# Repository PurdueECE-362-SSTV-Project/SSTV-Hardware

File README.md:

# SSTV-Hardware
This repo contains the SCHEM and PCB files for the SSTV Receiver.

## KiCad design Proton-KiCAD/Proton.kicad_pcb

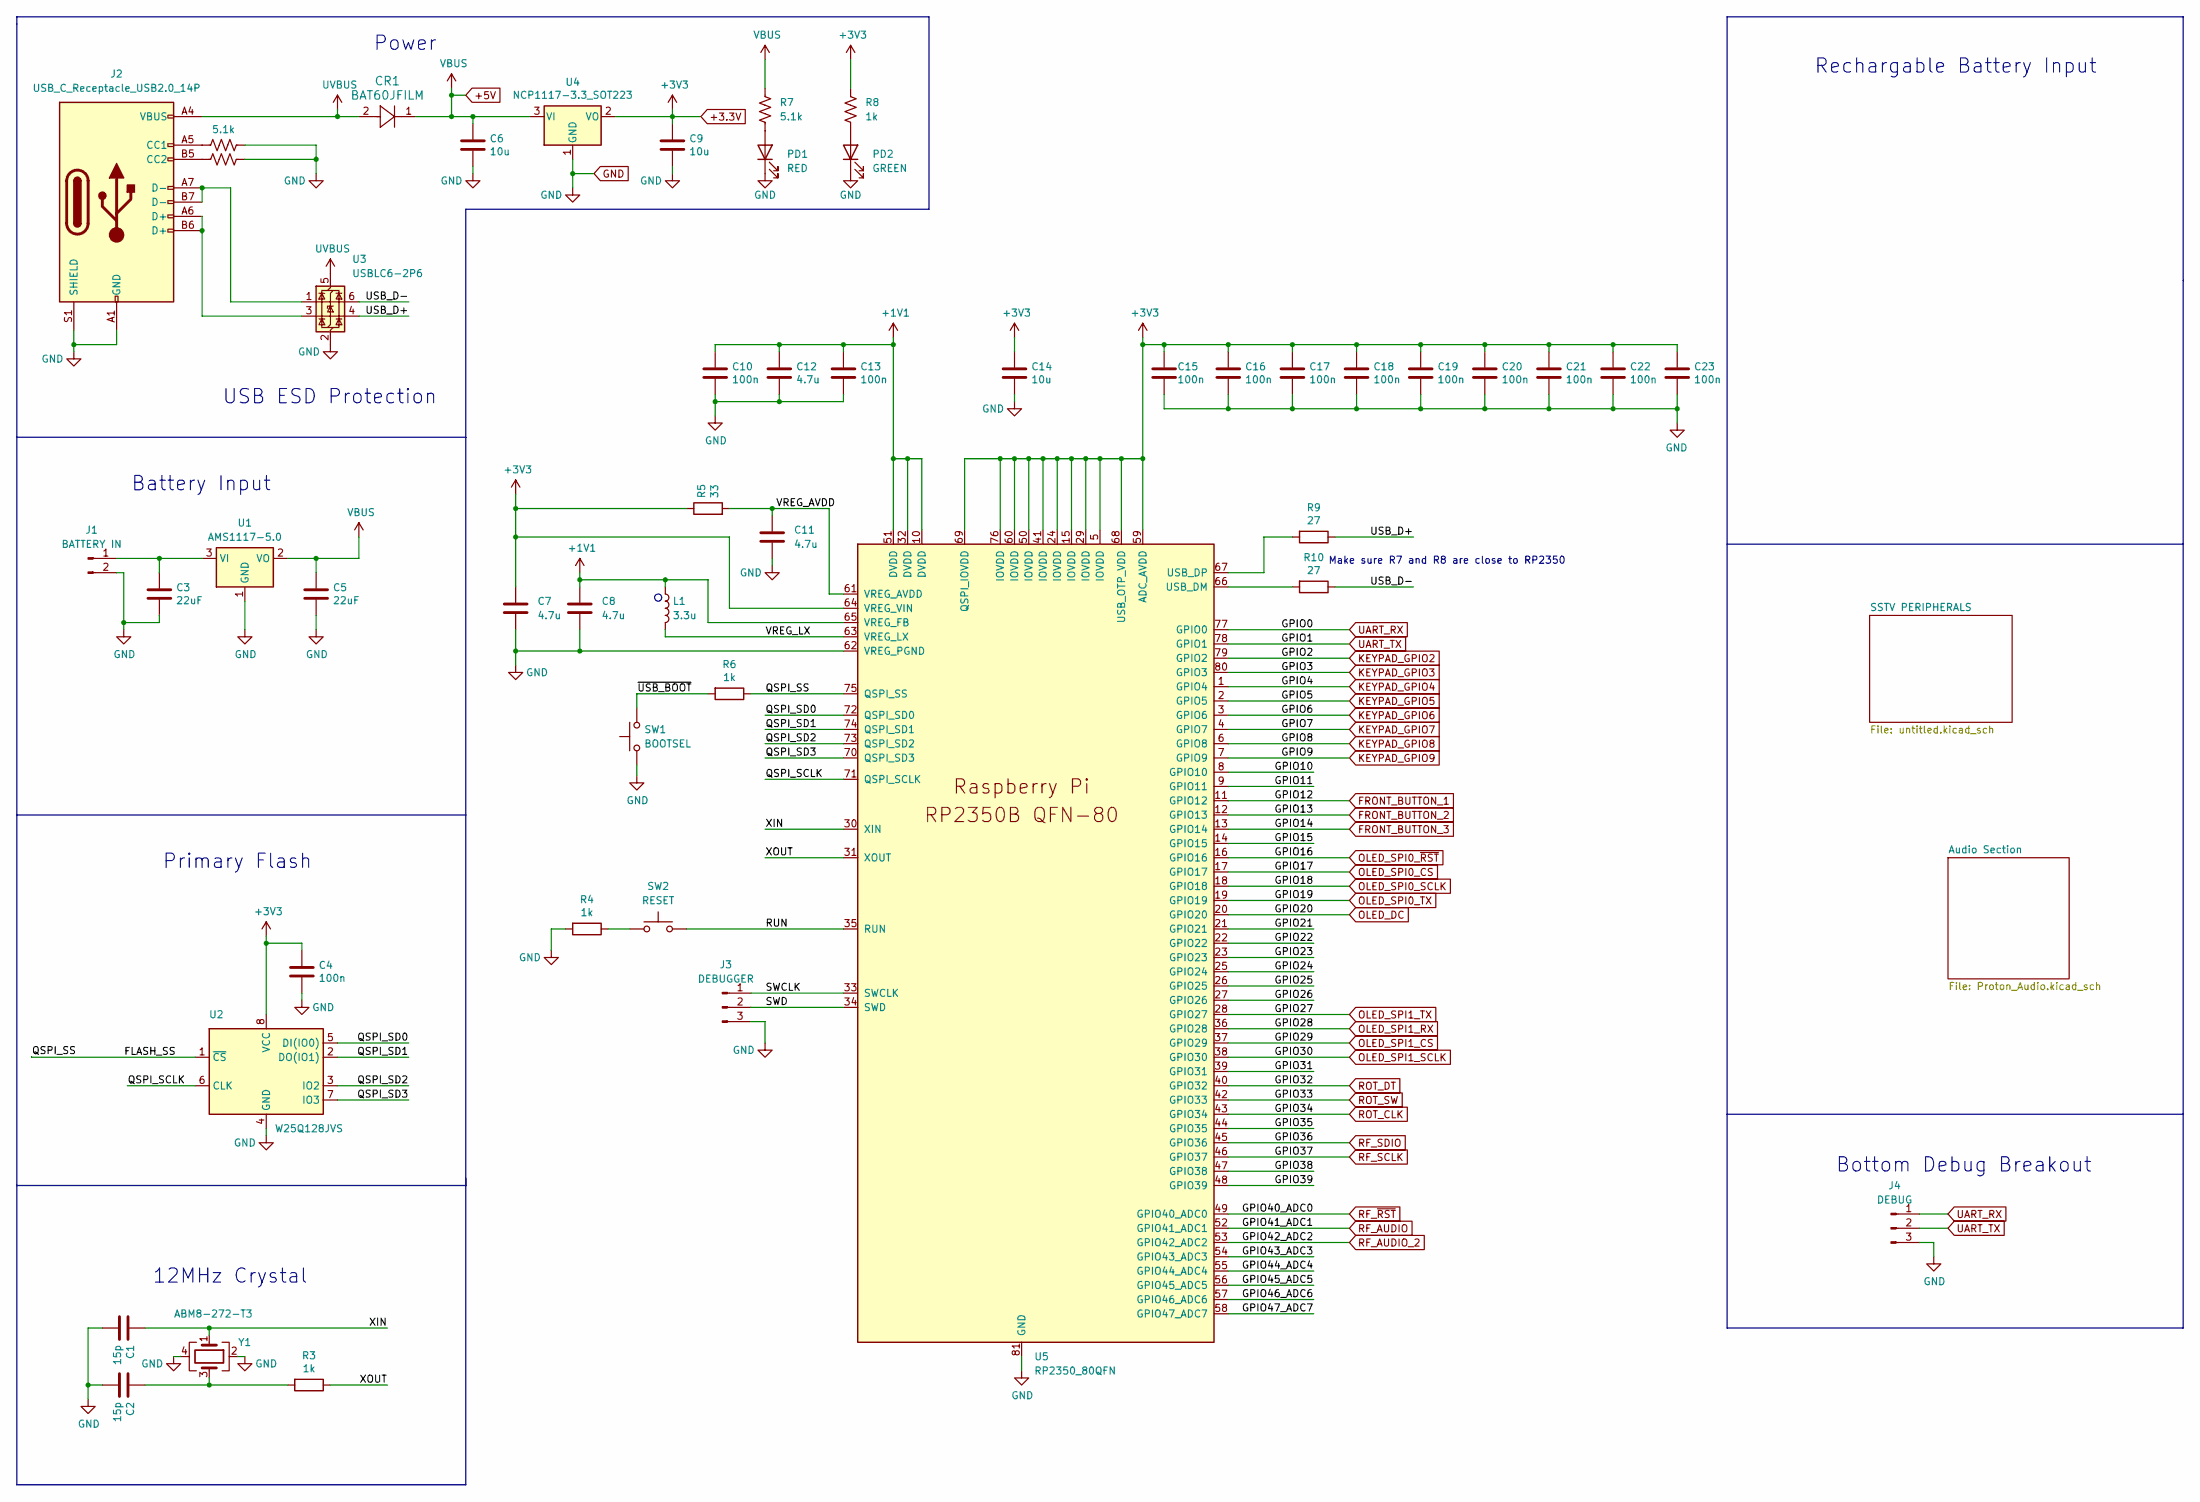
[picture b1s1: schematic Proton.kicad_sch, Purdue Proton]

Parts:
C1, C2: 15p; C_0402_1005Metric
C3, C5: 22uF; C_0805_2012Metric
C4, C10, C13, C15, C16, C17, C18, C19, C20, C21, C22, C23: 100n; C_0402_1005Metric
C6, C9, C14: 10u; C_0805_2012Metric
C7, C8, C11, C12: 4.7u; C_0402_1005Metric
CR1: BAT60JFILM; CR_60JFILM_STM-M
J1: BATTERY IN; PinHeader_1x02_P2.54mm_Vertical
J2: USB_C_Receptacle_USB2.0_14P; USB_C_Receptacle_G-Switch_GT-USB-7010ASV
J3: DEBUGGER; PinHeader_1x03_P2.54mm_Vertical
J4: DEBUG; PinHeader_1x03_P2.54mm_Vertical
L1: 3.3u; L_pol_2016
PD1: RED; LED_0805_2012Metric
PD2: GREEN; LED_0805_2012Metric
R1, R2, R7: 5.1k; R_0402_1005Metric
R3, R4, R6, R8: 1k; R_0402_1005Metric
R5: 33; R_0402_1005Metric
R9, R10: 27; R_0402_1005Metric
SW1: BOOTSEL; SW_SPST_PTS647_Sx38
SW2: RESET; SW_SPST_PTS647_Sx38
U1: AMS1117-5.0; SOT-223-3_TabPin2
U2: W25Q128JVS; SOIC-8_5.3x5.3mm_P1.27mm
U3: USBLC6-2P6; SOT-666
U4: NCP1117-3.3_SOT223; SOT-223-3_TabPin2
U5: RP2350_80QFN; QFN-80-1EP_10x10mm_P0.4mm_EP3.4x3.4mm_ThermalVias
Y1: ABM8-272-T3; Crystal_SMD_3225-4Pin_3.2x2.5mm

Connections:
+1V1: C8.1, C10.1, C12.1, C13.1, L1.1, U5.10 (DVDD), U5.32 (DVDD), U5.51 (DVDD), U5.65 (VREG_FB)
+3.3V: C4.1, C7.1, C9.1, C14.1, C15.1, C16.1, C17.1, C18.1, C19.1, C20.1, C21.1, C22.1, C23.1, R5.1, R8.1, U2.8 (VCC), U4.2 (VO), U5.5 (IOVDD), U5.15 (IOVDD), U5.24 (IOVDD), U5.29 (IOVDD), U5.41 (IOVDD), U5.50 (IOVDD), U5.59 (ADC_AVDD), U5.60 (IOVDD), U5.64 (VREG_VIN), U5.68 (USB_OTP_VDD), U5.69 (QSPI_IOVDD), U5.76 (IOVDD); also elsewhere on the board
+5V: C5.1, C6.1, CR1.1, R7.1, U1.2 (VO), U4.3 (VI); also elsewhere on the board
/FLASH_SS: R6.1, U2.1 (~CS), U5.75 (QSPI_SS)
/GPIO10: U5.8 (GPIO10)
/GPIO11: U5.9 (GPIO11)
/GPIO15: U5.14 (GPIO15)
/GPIO21: U5.21 (GPIO21)
/GPIO22: U5.22 (GPIO22)
/GPIO23: U5.23 (GPIO23)
/GPIO24: U5.25 (GPIO24)
/GPIO25: U5.26 (GPIO25)
/GPIO26: U5.27 (GPIO26)
/GPIO31: U5.39 (GPIO31)
/GPIO35: U5.44 (GPIO35)
/GPIO38: U5.47 (GPIO38)
/GPIO39: U5.48 (GPIO39)
/GPIO43_ADC3: U5.54 (GPIO43_ADC3)
/GPIO44_ADC4: U5.55 (GPIO44_ADC4)
/GPIO45_ADC5: U5.56 (GPIO45_ADC5)
/GPIO46_ADC6: U5.57 (GPIO46_ADC6)
/GPIO47_ADC7: U5.58 (GPIO47_ADC7)
/QSPI_SCLK: U2.6 (CLK), U5.71 (QSPI_SCLK)
/QSPI_SD0: U2.5 (DI(IO0)), U5.72 (QSPI_SD0)
/QSPI_SD1: U2.2 (DO(IO1)), U5.74 (QSPI_SD1)
/QSPI_SD2: U2.3 (IO2), U5.73 (QSPI_SD2)
/QSPI_SD3: U2.7 (IO3), U5.70 (QSPI_SD3)
/RUN: SW2.2, U5.35 (RUN)
/SWCLK: J3.1, U5.33 (SWCLK)
/SWD: J3.2, U5.34 (SWD)
/USB_D+: R9.1, U3.4 (I/O2)
/USB_D-: R10.1, U3.6 (I/O1)
/VREG_AVDD: C11.1, R5.2, U5.61 (VREG_AVDD)
/VREG_LX: L1.2, U5.63 (VREG_LX)
/XIN: C1.1, U5.30 (XIN), Y1.1
/XOUT: R3.1, U5.31 (XOUT)
/~USB_BOOT: R6.2, SW1.2
FRONT_BUTTON_1: U5.11 (GPIO12); also elsewhere on the board
FRONT_BUTTON_2: U5.12 (GPIO13); also elsewhere on the board
FRONT_BUTTON_3: U5.13 (GPIO14); also elsewhere on the board
GND: C1.2, C2.2, C3.2, C4.2, C5.2, C6.2, C7.2, C8.2, C9.2, C10.2, C11.2, C12.2, C13.2, C14.2, C15.2, C16.2, C17.2, C18.2, C19.2, C20.2, C21.2, C22.2, C23.2, J1.2, J2.A1 (GND), J2.A12 (GND), J2.B1 (GND), J2.B12 (GND), J2.S1 (SHIELD), J3.3, J4.3, PD1.1 (K), PD2.1 (K), R1.2, R2.2, R4.2, SW1.1, U1.1 (GND), U2.4 (GND), U3.2 (GND), U4.1 (GND), U5.62 (VREG_PGND), U5.81 (GND), Y1.2, Y1.4; also elsewhere on the board
KEYPAD_GPIO2: U5.79 (GPIO2); also elsewhere on the board
KEYPAD_GPIO3: U5.80 (GPIO3); also elsewhere on the board
KEYPAD_GPIO4: U5.1 (GPIO4); also elsewhere on the board
KEYPAD_GPIO5: U5.2 (GPIO5); also elsewhere on the board
KEYPAD_GPIO6: U5.3 (GPIO6); also elsewhere on the board
KEYPAD_GPIO7: U5.4 (GPIO7); also elsewhere on the board
KEYPAD_GPIO8: U5.6 (GPIO8); also elsewhere on the board
KEYPAD_GPIO9: U5.7 (GPIO9); also elsewhere on the board
unnamed: C2.1, R3.2, Y1.3
unnamed: C3.1, J1.1, U1.3 (VI)
unnamed: J2.A5 (CC1), R1.1
unnamed: J2.B5 (CC2), R2.1
unnamed: J2.A6 (D+), J2.B6 (D+), U3.3 (I/O2)
unnamed: J2.A7 (D-), J2.B7 (D-), U3.1 (I/O1)
unnamed: PD1.2 (A), R7.2
unnamed: PD2.2 (A), R8.2
unnamed: R4.1, SW2.1
unnamed: R10.2, U5.66 (USB_DM)
unnamed: R9.2, U5.67 (USB_DP)
OLED_DC: U5.20 (GPIO20); also elsewhere on the board
OLED_SPI0_CS: U5.17 (GPIO17); also elsewhere on the board
OLED_SPI0_SCLK: U5.18 (GPIO18); also elsewhere on the board
OLED_SPI0_TX: U5.19 (GPIO19); also elsewhere on the board
OLED_SPI0_~RST: U5.16 (GPIO16); also elsewhere on the board
OLED_SPI1_CS: U5.37 (GPIO29); also elsewhere on the board
OLED_SPI1_RX: U5.36 (GPIO28); also elsewhere on the board
OLED_SPI1_SCLK: U5.38 (GPIO30); also elsewhere on the board
OLED_SPI1_TX: U5.28 (GPIO27); also elsewhere on the board
RF_AUDIO: U5.52 (GPIO41_ADC1); also elsewhere on the board
RF_AUDIO_2: U5.53 (GPIO42_ADC2); also elsewhere on the board
RF_SCLK: U5.46 (GPIO37); also elsewhere on the board
RF_SDIO: U5.45 (GPIO36); also elsewhere on the board
RF_~RST: U5.49 (GPIO40_ADC0); also elsewhere on the board
ROT_CLK: U5.43 (GPIO34); also elsewhere on the board
ROT_DT: U5.40 (GPIO32); also elsewhere on the board
ROT_SW: U5.42 (GPIO33); also elsewhere on the board
UART_RX: J4.1, U5.77 (GPIO0)
UART_TX: J4.2, U5.78 (GPIO1)
UVBUS: CR1.2, J2.A4 (VBUS), J2.A9 (VBUS), J2.B4 (VBUS), J2.B9 (VBUS), U3.5 (VBUS)

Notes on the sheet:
12MHz Crystal
Bottom Debug Breakout
Primary Flash
Make sure R7 and R8 are close to RP2350
Battery Input
USB ESD Protection
Rechargable Battery Input
Power

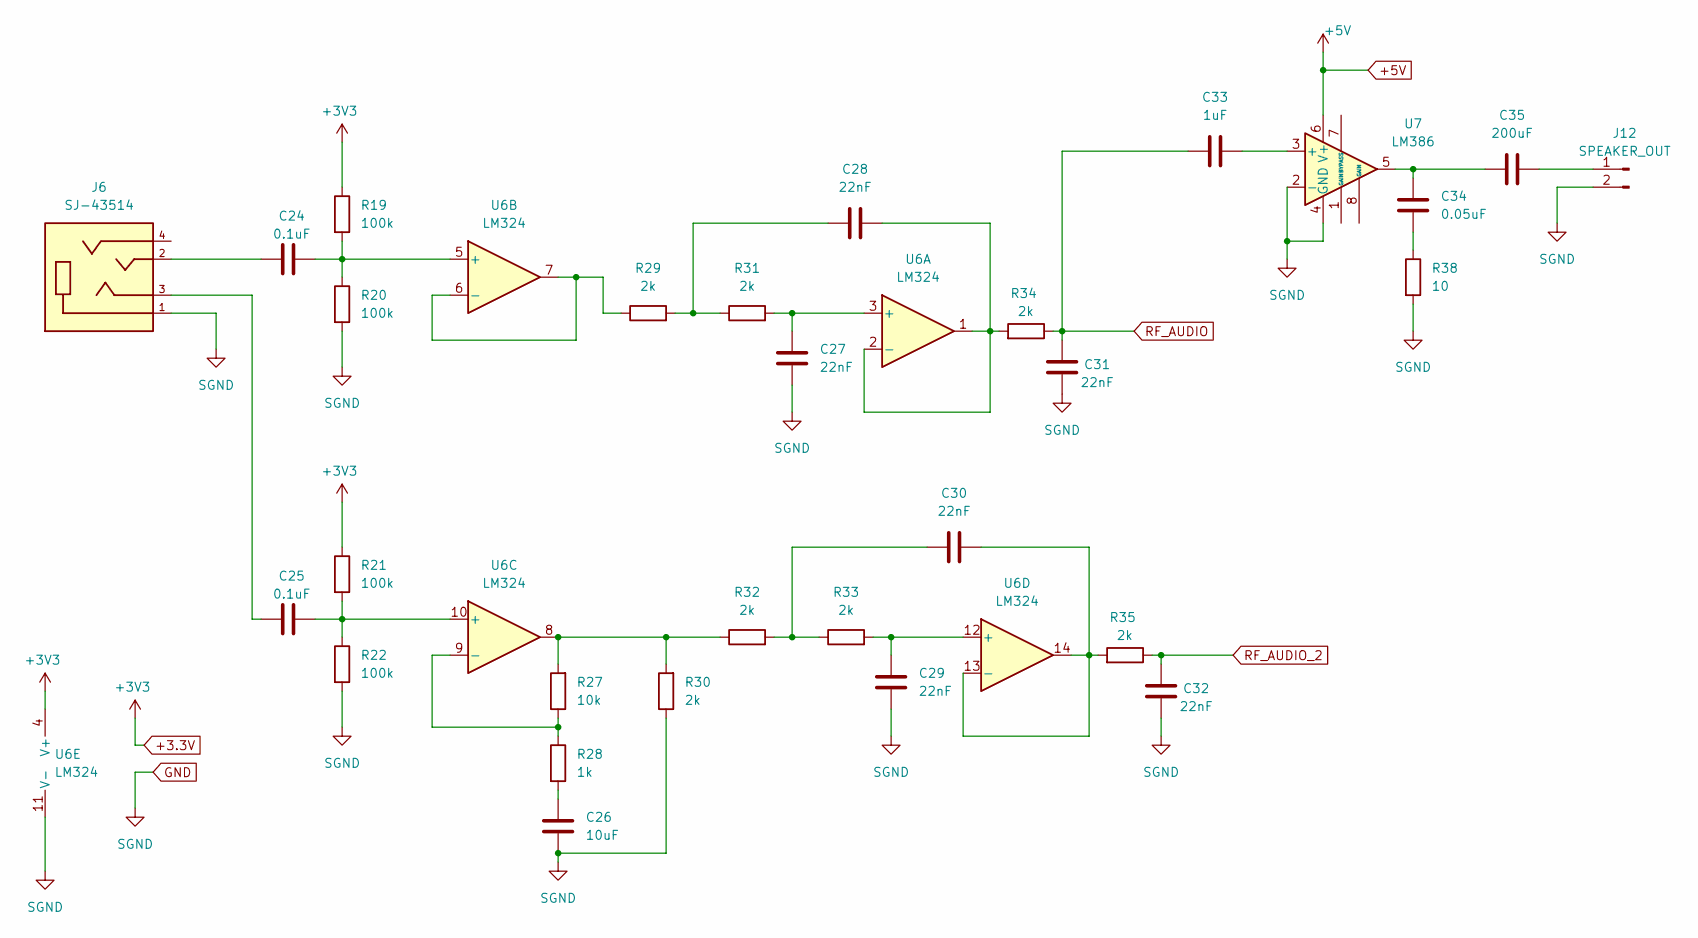
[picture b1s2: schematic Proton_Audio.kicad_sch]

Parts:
C24, C25: 0.1uF; C_0402_1005Metric
C26: 10uF; C_0805_2012Metric
C27, C28, C29, C30, C31, C32: 22nF; C_0402_1005Metric
C33: 1uF; C_0402_1005Metric
C34: 0.05uF; C_0402_1005Metric
C35: 200uF; CP_Elec_6.3x4.5
J6: SJ-43514; CUI_SJ-43514; PART_REV 1.04
J12: SPEAKER_OUT; PinHeader_1x02_P2.54mm_Vertical
R19, R20, R21, R22: 100k; R_0402_1005Metric
R27: 10k; R_0402_1005Metric
R28: 1k; R_0402_1005Metric
R29, R30, R31, R32, R33, R34, R35: 2k; R_0402_1005Metric
R38: 10; R_0402_1005Metric
U6: LM324; DIP-14_W7.62mm
U7: LM386; DIP-8_W7.62mm

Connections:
+3.3V: R19.1, R21.1, U6.4 (V+); also elsewhere on the board
+5V: U7.6 (V+); also elsewhere on the board
GND: C26.2, C27.2, C29.2, C31.2, C32.2, J6.1, J12.2, R20.2, R22.2, R30.1, R38.2, U6.11 (V-), U7.2 (-), U7.4 (GND); also elsewhere on the board
unnamed: C24.1, J6.2
unnamed: C25.1, J6.3
unnamed: C26.1, R28.2
unnamed: C28.1, R29.2, R31.1
unnamed: C30.1, R32.2, R33.1
unnamed: C34.1, R38.1
unnamed: C34.2, C35.2, U7.5
unnamed: C35.1, J12.1
unnamed: R27.2, R30.2, R32.1, U6.8
unnamed: C27.1, R31.2, U6.3 (+)
unnamed: C28.2, R34.2, U6.1, U6.2 (-)
unnamed: C24.2, R19.2, R20.1, U6.5 (+)
unnamed: R29.1, U6.6 (-), U6.7
unnamed: C25.2, R21.2, R22.1, U6.10 (+)
unnamed: R27.1, R28.1, U6.9 (-)
unnamed: C29.1, R33.2, U6.12 (+)
unnamed: C30.2, R35.2, U6.13 (-), U6.14
unnamed: C33.2, U7.3 (+)
RF_AUDIO: C31.1, C33.1, R34.1; also elsewhere on the board
RF_AUDIO_2: C32.1, R35.1; also elsewhere on the board

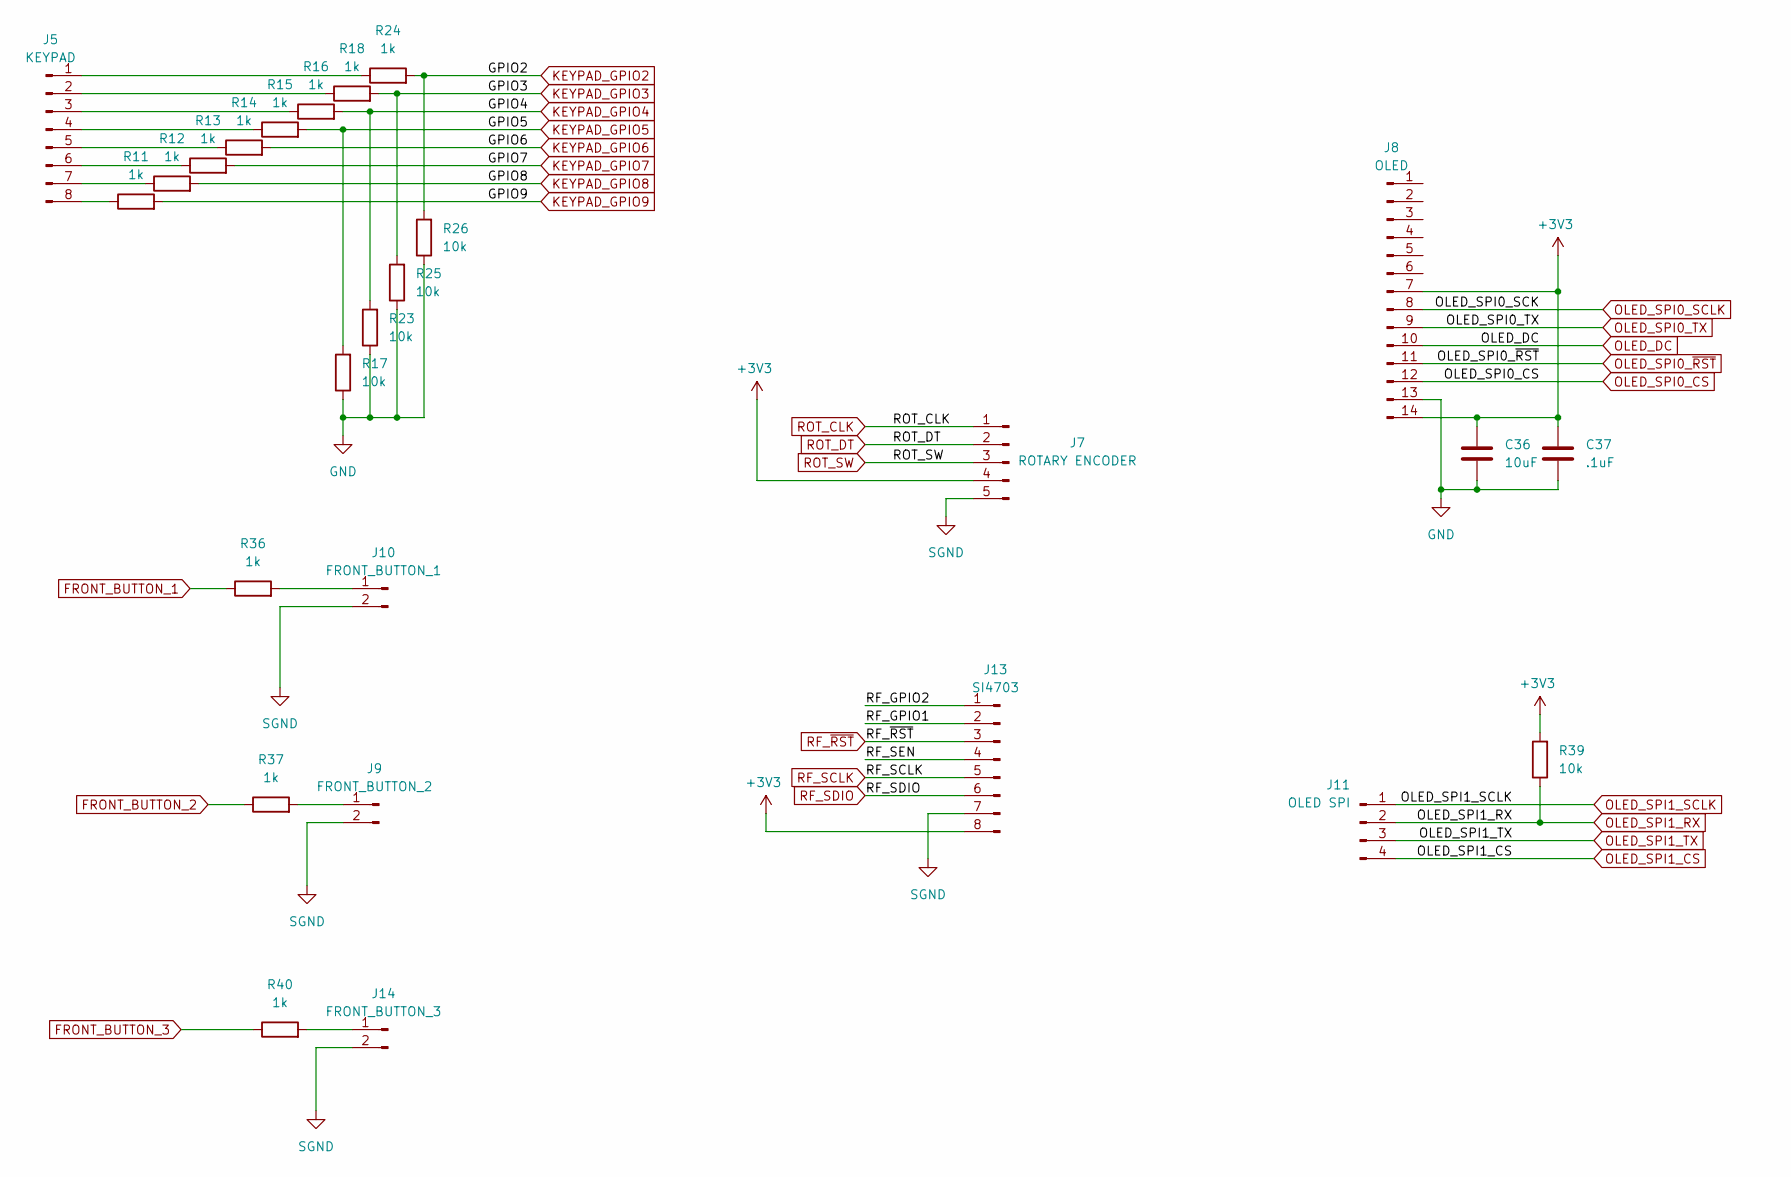
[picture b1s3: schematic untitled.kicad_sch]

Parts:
C36: 10uF; C_0805_2012Metric
C37: .1uF; C_0402_1005Metric
J5: KEYPAD; PinHeader_1x08_P2.54mm_Vertical
J7: ROTARY ENCODER; PinHeader_1x05_P2.54mm_Vertical
J8: OLED; PinHeader_1x14_P2.54mm_Vertical
J9: FRONT_BUTTON_2; PinHeader_1x02_P2.54mm_Vertical
J10: FRONT_BUTTON_1; PinHeader_1x02_P2.54mm_Vertical
J11: OLED SPI; PinHeader_1x04_P2.54mm_Vertical
J13: SI4703; PinHeader_1x08_P2.54mm_Vertical
J14: FRONT_BUTTON_3; PinHeader_1x02_P2.54mm_Vertical
R11, R12, R13, R14, R15, R16, R18, R24, R36, R37, R40: 1k; R_0402_1005Metric
R17, R23, R25, R26, R39: 10k; R_0402_1005Metric

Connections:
+3.3V: C36.1, C37.1, J7.4, J8.7, J8.14, J13.8, R39.2; also elsewhere on the board
/SSTV PERIPHERALS/RF_GPIO1: J13.2
/SSTV PERIPHERALS/RF_GPIO2: J13.1
/SSTV PERIPHERALS/RF_SEN: J13.4
FRONT_BUTTON_1: R36.1; also elsewhere on the board
FRONT_BUTTON_2: R37.1; also elsewhere on the board
FRONT_BUTTON_3: R40.1; also elsewhere on the board
GND: C36.2, C37.2, J7.5, J8.13, J9.2, J10.2, J13.7, J14.2, R17.1, R23.1, R25.1, R26.1; also elsewhere on the board
KEYPAD_GPIO2: R24.2, R26.2; also elsewhere on the board
KEYPAD_GPIO3: R18.2, R25.2; also elsewhere on the board
KEYPAD_GPIO4: R16.2, R23.2; also elsewhere on the board
KEYPAD_GPIO5: R15.2, R17.2; also elsewhere on the board
KEYPAD_GPIO6: R14.2; also elsewhere on the board
KEYPAD_GPIO7: R13.2; also elsewhere on the board
KEYPAD_GPIO8: R12.2; also elsewhere on the board
KEYPAD_GPIO9: R11.2; also elsewhere on the board
unnamed: J5.1, R24.1
unnamed: J5.2, R18.1
unnamed: J5.3, R16.1
unnamed: J5.4, R15.1
unnamed: J5.5, R14.1
unnamed: J5.6, R13.1
unnamed: J5.7, R12.1
unnamed: J5.8, R11.1
unnamed: J9.1, R37.2
unnamed: J10.1, R36.2
unnamed: J14.1, R40.2
OLED_DC: J8.10; also elsewhere on the board
OLED_SPI0_CS: J8.12; also elsewhere on the board
OLED_SPI0_SCLK: J8.8; also elsewhere on the board
OLED_SPI0_TX: J8.9; also elsewhere on the board
OLED_SPI0_~RST: J8.11; also elsewhere on the board
OLED_SPI1_CS: J11.4; also elsewhere on the board
OLED_SPI1_RX: J11.2, R39.1; also elsewhere on the board
OLED_SPI1_SCLK: J11.1; also elsewhere on the board
OLED_SPI1_TX: J11.3; also elsewhere on the board
RF_SCLK: J13.5; also elsewhere on the board
RF_SDIO: J13.6; also elsewhere on the board
RF_~RST: J13.3; also elsewhere on the board
ROT_CLK: J7.1; also elsewhere on the board
ROT_DT: J7.2; also elsewhere on the board
ROT_SW: J7.3; also elsewhere on the board

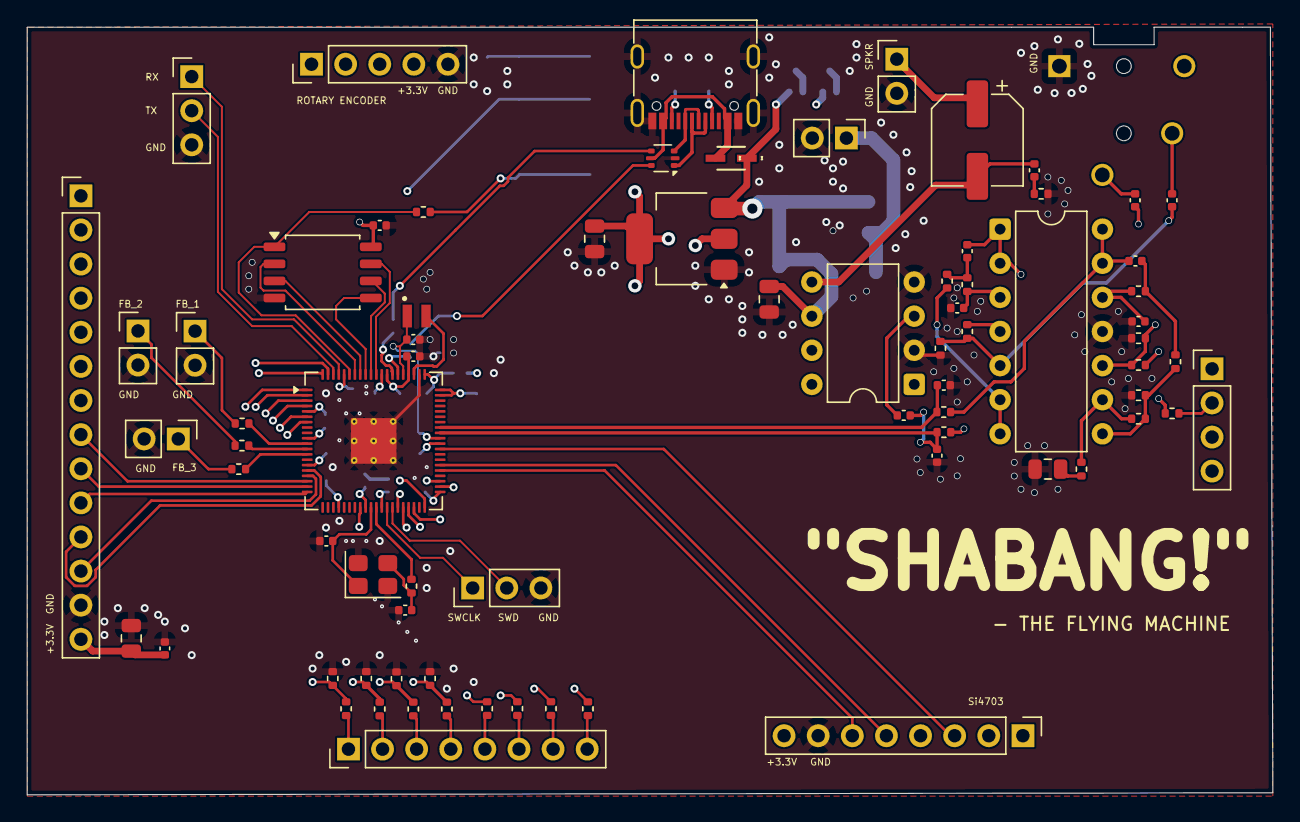
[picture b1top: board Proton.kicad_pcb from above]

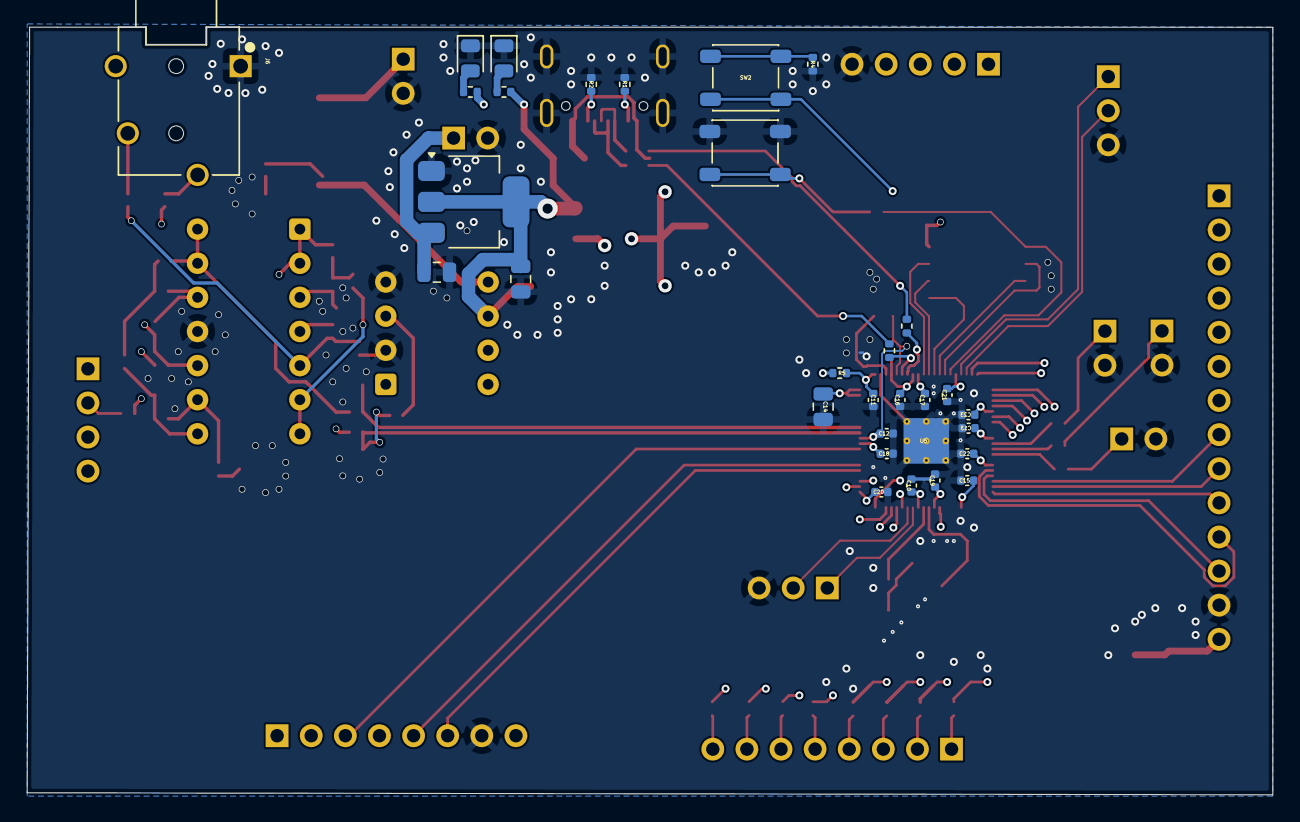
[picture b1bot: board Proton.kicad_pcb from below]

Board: 4 copper layers, 92.8 x 57.2 mm, 105 parts (30 on the bottom side), 91 nets.

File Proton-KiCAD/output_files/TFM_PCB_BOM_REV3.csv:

Reference,Value,Footprint,Footprint,
"C1,C2",15p,Capacitor_SMD:C_0402_1005Metric,Capacitor_SMD:C_0402_1005Metric,C1548
"C3,C5",22uF,Capacitor_SMD:C_0805_2012Metric,Capacitor_SMD:C_0805_2012Metric,C5674
"C4,C10,C13,C15,C16,C17,C18,C19,C20,C21,C22,C23",100n,Capacitor_SMD:C_0402_1005Metric,Capacitor_SMD:C_0402_1005Metric,C1525
"C6,C9,C14",10u,Capacitor_SMD:C_0805_2012Metric,Capacitor_SMD:C_0805_2012Metric,C15850
"C7,C8,C11,C12",4.7u,Capacitor_SMD:C_0402_1005Metric,Capacitor_SMD:C_0402_1005Metric,C23733
"C24,C25",0.1uF,Capacitor_SMD:C_0402_1005Metric,Capacitor_SMD:C_0402_1005Metric,C77012
"C26,C36",10uF,Capacitor_SMD:C_0805_2012Metric,Capacitor_SMD:C_0805_2012Metric,C15850
"C27,C28,C29,C30,C31,C32",22nF,Capacitor_SMD:C_0402_1005Metric,Capacitor_SMD:C_0402_1005Metric,C1532
C33,1uF,Capacitor_SMD:C_0402_1005Metric,Capacitor_SMD:C_0402_1005Metric,C52923
C34,0.05uF,Capacitor_SMD:C_0402_1005Metric,Capacitor_SMD:C_0402_1005Metric,C1525
C35,200uF,Capacitor_SMD:CP_Elec_6.3x4.5,Capacitor_SMD:CP_Elec_6.3x4.5,C51953393
C37,.1uF,Capacitor_SMD:C_0402_1005Metric,Capacitor_SMD:C_0402_1005Metric,C1525
CR1,BAT60JFILM,diode shite:CR_60JFILM_STM-M,diode shite:CR_60JFILM_STM-M,C133103
,,,,
J2,USB_C_Receptacle_USB2.0_14P,Connector_USB:USB_C_Receptacle_G-Switch_GT-USB-7010ASV,Connector_USB:USB_C_Receptacle_G-Switch_GT-USB-7010ASV,C2988369
,,,,
,,,,
,,,,
,,,,
,,,,
,,,,
,,,,
,,,,
,,,,
,,,,
,,,,
,,,,
L1,3.3u,Custom:L_pol_2016,Custom:L_pol_2016,C42411119
PD1,RED,LED_SMD:LED_0805_2012Metric,LED_SMD:LED_0805_2012Metric,C84256
PD2,GREEN,LED_SMD:LED_0805_2012Metric,LED_SMD:LED_0805_2012Metric,C2297
"R1,R2,R7",5.1k,Resistor_SMD:R_0402_1005Metric,Resistor_SMD:R_0402_1005Metric,C25905
"R3,R4,R6,R8,R11,R12,R13,R14,R15,R16,R18,R24,R28,R36,R37,R40",1k,Resistor_SMD:R_0402_1005Metric,Resistor_SMD:R_0402_1005Metric,C11702
R5,33,Resistor_SMD:R_0402_1005Metric,Resistor_SMD:R_0402_1005Metric,C25105
"R9,R10",27,Resistor_SMD:R_0402_1005Metric,Resistor_SMD:R_0402_1005Metric,C20625731
"R17,R23,R25,R26,R39",10k,Resistor_SMD:R_0402_1005Metric,Resistor_SMD:R_0402_1005Metric,C25531
"R19,R20,R21,R22",100k,Resistor_SMD:R_0402_1005Metric,Resistor_SMD:R_0402_1005Metric,C176119
R27,10k,Resistor_SMD:R_0402_1005Metric,Resistor_SMD:R_0402_1005Metric,C25531
"R29,R30,R31,R32,R33,R34,R35",2k,Resistor_SMD:R_0402_1005Metric,Resistor_SMD:R_0402_1005Metric,C4109
R38,10,Resistor_SMD:R_0402_1005Metric,Resistor_SMD:R_0402_1005Metric,C174147
SW1,BOOTSEL,Button_Switch_SMD:SW_SPST_PTS647_Sx38,Button_Switch_SMD:SW_SPST_PTS647_Sx38,C2689502
SW2,RESET,Button_Switch_SMD:SW_SPST_PTS647_Sx38,Button_Switch_SMD:SW_SPST_PTS647_Sx38,C2689502
U1,AMS1117-5.0,Package_TO_SOT_SMD:SOT-223-3_TabPin2,Package_TO_SOT_SMD:SOT-223-3_TabPin2,C6187
U2,W25Q128JVS,Package_SO:SOIC-8_5.3x5.3mm_P1.27mm,Package_SO:SOIC-8_5.3x5.3mm_P1.27mm,C97521
U3,USBLC6-2P6,Package_TO_SOT_SMD:SOT-666,Package_TO_SOT_SMD:SOT-666,C15999
U4,NCP1117-3.3_SOT223,Package_TO_SOT_SMD:SOT-223-3_TabPin2,Package_TO_SOT_SMD:SOT-223-3_TabPin2,C26537
U5,RP2350_80QFN,Package_DFN_QFN:QFN-80-1EP_10x10mm_P0.4mm_EP3.4x3.4mm_ThermalVias,Package_DFN_QFN:QFN-80-1EP_10x10mm_P0.4mm_EP3.4x3.4mm_ThermalVias,C42415655
,,,,
,,,,
Y1,ABM8-272-T3,Crystal:Crystal_SMD_3225-4Pin_3.2x2.5mm,Crystal:Crystal_SMD_3225-4Pin_3.2x2.5mm,C20625731

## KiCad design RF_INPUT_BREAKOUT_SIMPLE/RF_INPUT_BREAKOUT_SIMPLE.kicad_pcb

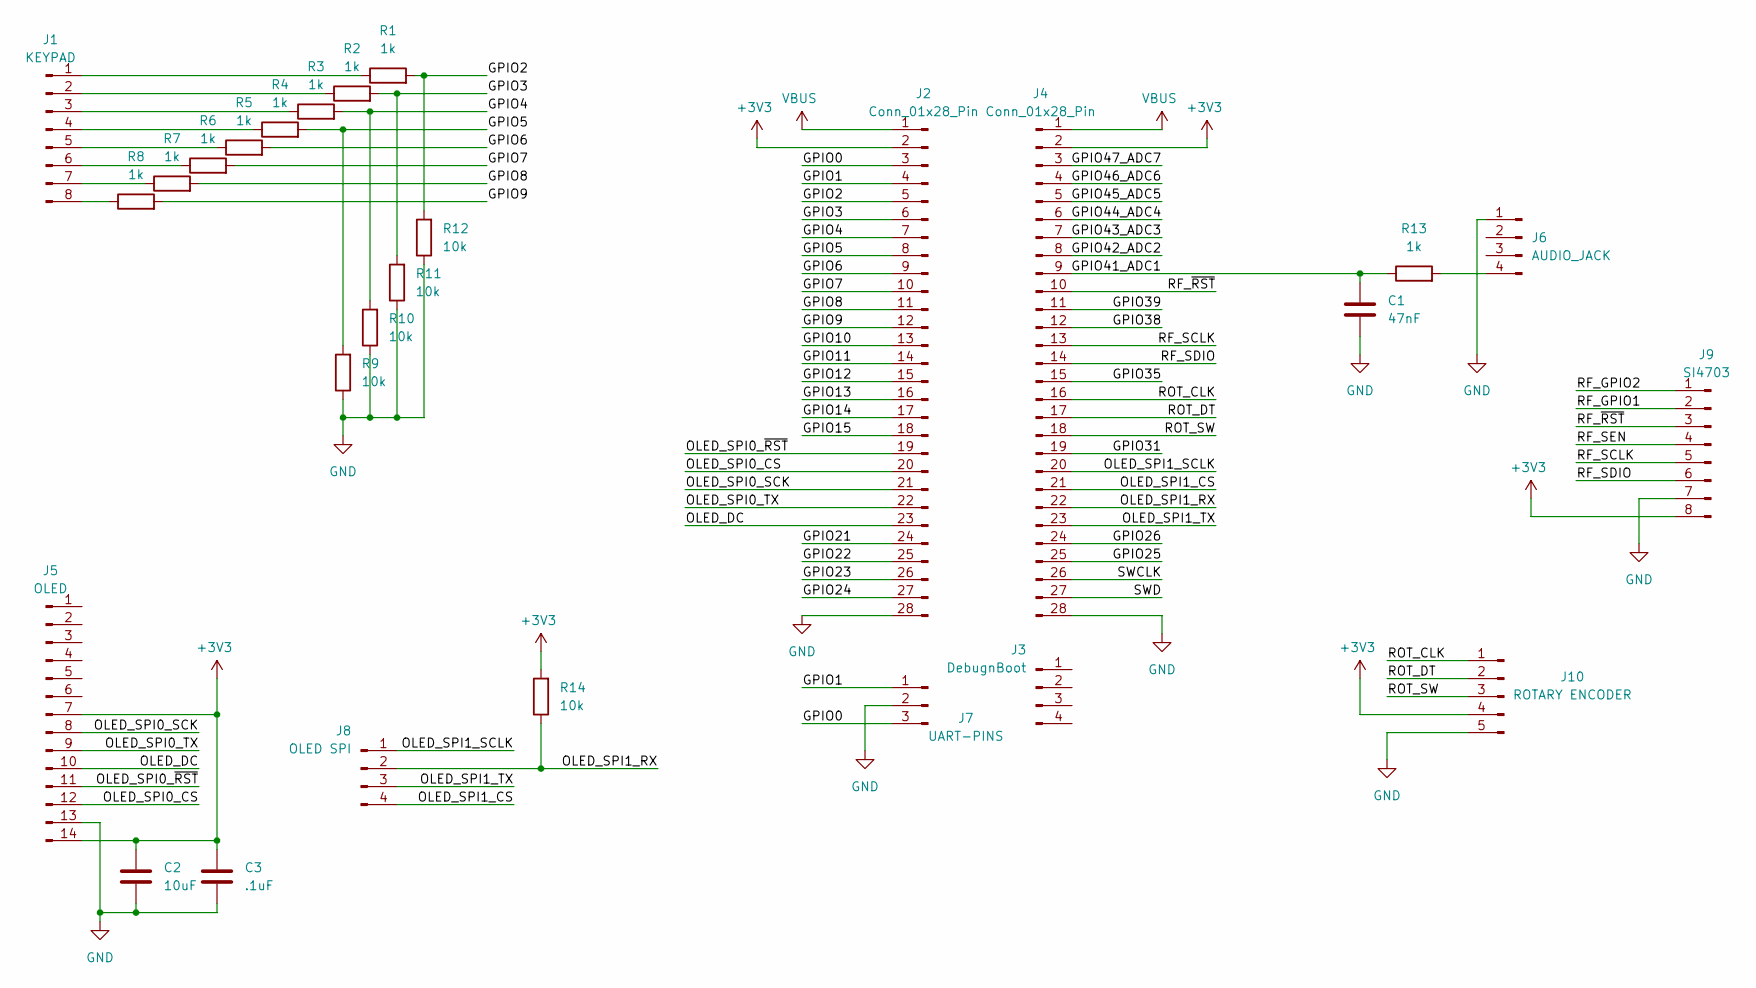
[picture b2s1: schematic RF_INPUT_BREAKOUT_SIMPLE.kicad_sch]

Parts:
C1: 47nF; C_0805_2012Metric
C2: 10uF; C_0805_2012Metric
C3: .1uF; C_0805_2012Metric
J1: KEYPAD; PinHeader_1x08_P2.54mm_Vertical
J2, J4: Conn_01x28_Pin; PinHeader_1x28_P2.54mm_Vertical
J3: DebugnBoot; PinHeader_1x04_P2.54mm_Vertical
J5: OLED; PinHeader_1x14_P2.54mm_Vertical
J6: AUDIO_JACK; PinHeader_1x04_P2.54mm_Vertical
J7: UART-PINS; PinHeader_1x03_P2.54mm_Vertical
J8: OLED SPI; PinHeader_1x04_P2.54mm_Vertical
J9: SI4703; PinHeader_1x08_P2.54mm_Vertical
J10: ROTARY ENCODER; PinHeader_1x05_P2.54mm_Vertical
R1, R2, R3, R4, R5, R6, R7, R8, R13: 1k; R_0805_2012Metric
R9, R10, R11, R12, R14: 10k; R_0805_2012Metric

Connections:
+3V3: C2.1, C3.1, J2.2, J4.2, J5.7, J5.14, J9.8, J10.4, R14.2
/GPIO0: J2.3, J7.3
/GPIO1: J2.4, J7.1
/GPIO2: J2.5, R1.2, R12.2
/GPIO3: J2.6, R2.2, R11.2
/GPIO4: J2.7, R3.2, R10.2
/GPIO5: J2.8, R4.2, R9.2
/GPIO6: J2.9, R5.2
/GPIO7: J2.10, R6.2
/GPIO8: J2.11, R7.2
/GPIO9: J2.12, R8.2
/GPIO10: J2.13
/GPIO11: J2.14
/GPIO12: J2.15
/GPIO13: J2.16
/GPIO14: J2.17
/GPIO15: J2.18
/GPIO21: J2.24
/GPIO22: J2.25
/GPIO23: J2.26
/GPIO24: J2.27
/GPIO25: J4.25
/GPIO26: J4.24
/GPIO31: J4.19
/GPIO35: J4.15
/GPIO38: J4.12
/GPIO39: J4.11
/GPIO41_ADC1: C1.1, J4.9, R13.1
/GPIO42_ADC2: J4.8
/GPIO43_ADC3: J4.7
/GPIO44_ADC4: J4.6
/GPIO45_ADC5: J4.5
/GPIO46_ADC6: J4.4
/GPIO47_ADC7: J4.3
/OLED_DC: J2.23, J5.10
/OLED_SPI0_CS: J2.20, J5.12
/OLED_SPI0_SCK: J2.21, J5.8
/OLED_SPI0_TX: J2.22, J5.9
/OLED_SPI0_~RST: J2.19, J5.11
/OLED_SPI1_CS: J4.21, J8.4
/OLED_SPI1_RX: J4.22, J8.2, R14.1
/OLED_SPI1_SCLK: J4.20, J8.1
/OLED_SPI1_TX: J4.23, J8.3
/RF_GPIO1: J9.2
/RF_GPIO2: J9.1
/RF_SCLK: J4.13, J9.5
/RF_SDIO: J4.14, J9.6
/RF_SEN: J9.4
/RF_~RST: J4.10, J9.3
/ROT_CLK: J4.16, J10.1
/ROT_DT: J4.17, J10.2
/ROT_SW: J4.18, J10.3
/SWCLK: J4.26
/SWD: J4.27
GND: C1.2, C2.2, C3.2, J2.28, J4.28, J5.13, J6.1, J7.2, J9.7, J10.5, R9.1, R10.1, R11.1, R12.1
unnamed: J1.1, R1.1
unnamed: J1.2, R2.1
unnamed: J1.3, R3.1
unnamed: J1.4, R4.1
unnamed: J1.5, R5.1
unnamed: J1.6, R6.1
unnamed: J1.7, R7.1
unnamed: J1.8, R8.1
unnamed: J6.4, R13.2
VBUS: J2.1, J4.1

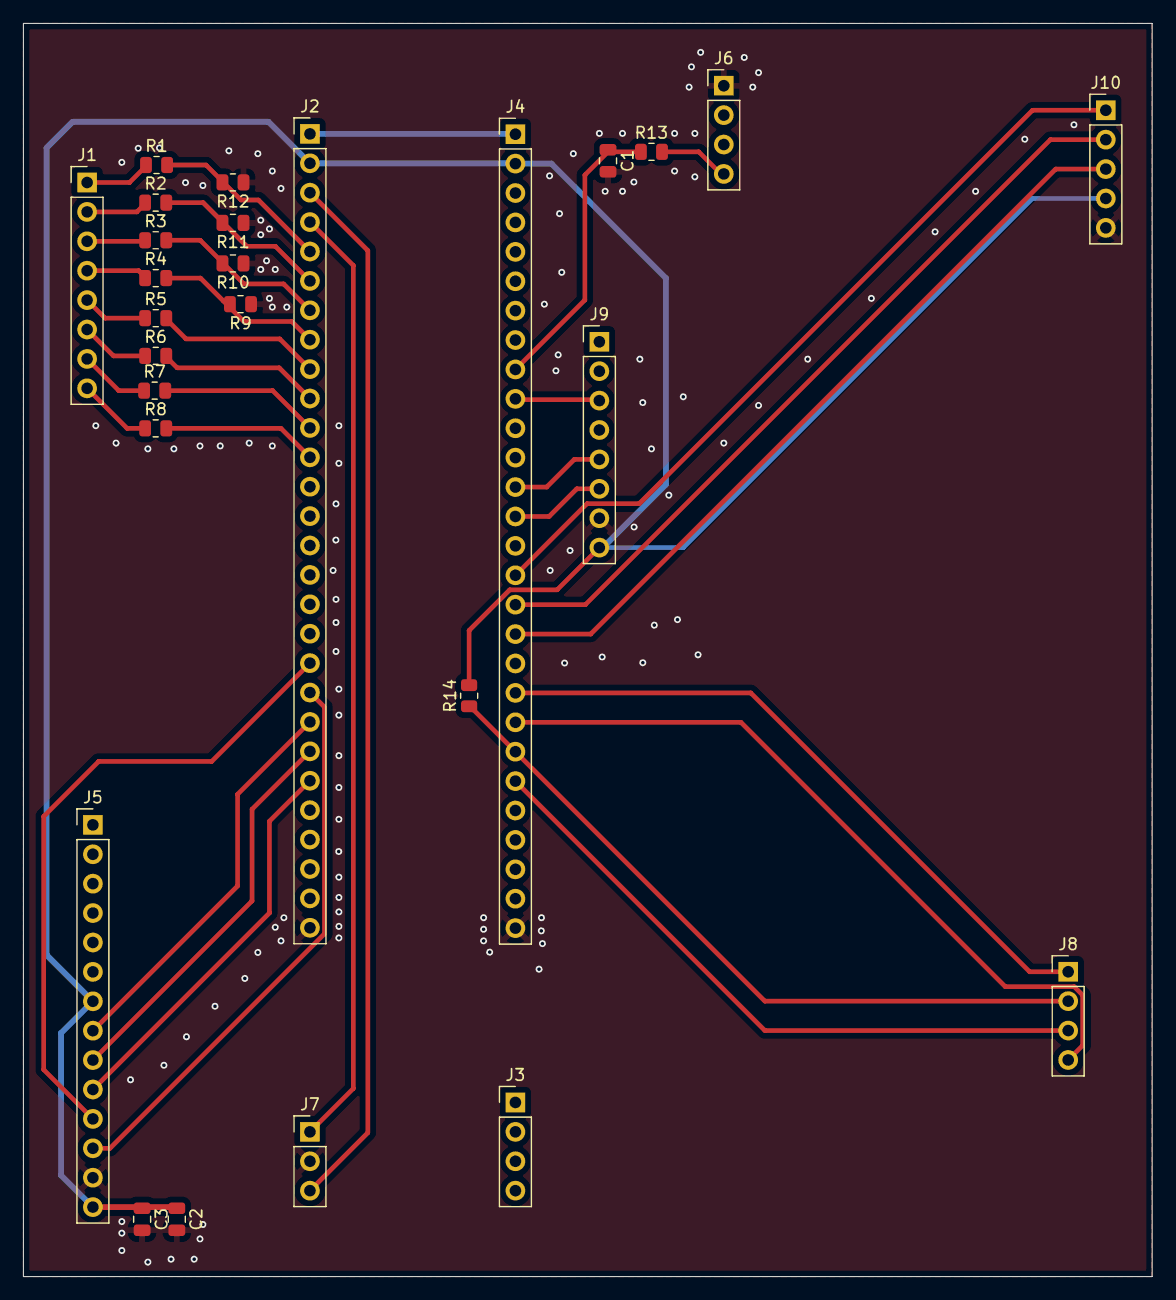
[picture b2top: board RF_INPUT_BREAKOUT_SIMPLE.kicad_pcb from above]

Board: 2 copper layers, 97.5 x 108.2 mm, 27 parts (0 on the bottom side), 38 nets.

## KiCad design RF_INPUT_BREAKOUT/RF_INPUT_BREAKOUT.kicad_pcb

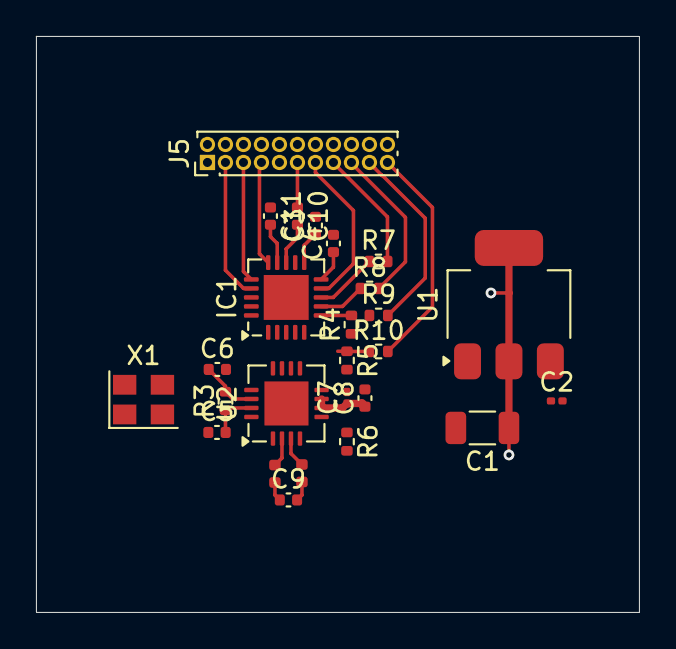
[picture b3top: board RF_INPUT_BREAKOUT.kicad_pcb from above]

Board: 4 copper layers, 33.5 x 32.0 mm, 26 parts (0 on the bottom side), 26 nets.

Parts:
C1: 10uF; C_1206_3216Metric
C2: .1uF; C_0201_0603Metric
C3: 22nF; C_0402_1005Metric
C4: .1uF; C_0402_1005Metric
C5, C6, C8: .01uF; C_0402_1005Metric
C7: 1uF; C_0201_0603Metric
C9: 33pF; C_0402_1005Metric
C10, C11: 1uF; C_0402_1005Metric
IC1: SI4705-D62-GM; QFN-20-1EP_4x4mm_P0.5mm_EP2.5x2.5mm
J5: Conn_2Rows-21Pins; PinHeader_2x11_P1.00mm_Vertical
L1, L2: 12nH; L_0402_1005Metric
R3: 100; R_0402_1005Metric
R4, R5, R6: 10k; R_0402_1005Metric
R7, R8, R9, R10: 330; R_0402_1005Metric
U1: LD1117S33TR_SOT223; SOT-223-3_TabPin2
U2: LT5512EUF-PBF; QFN-16-1EP_4x4mm_P0.5mm_EP2.45x2.45mm
X1: ASE-xxxMHz; Oscillator_SMD_Abracon_ASE-4Pin_3.2x2.5mm

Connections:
+3.3V: C1.1, C3.1, C4.1, IC1.10 (VD), IC1.11 (VA), R4.1, U1.2 (VO)
+5V: C2.1, C7.1, C8.1, U1.3 (VI), U2.6 (VCC1), U2.7 (VCC2)
/MCU_I2C_SCLK: IC1.7 (SCLK), R8.1
/MCU_I2S_SDIO: IC1.8 (SDIO), R7.1
/MCU_MIX_EN 3V: J5.2, R6.1, U2.5 (EN)
/MCU_RF_RCLK: IC1.9 (RCLK), J5.13
/MCU_RF_RST: IC1.5 (~RST), R5.1, R10.1
/MCU_RF_SEN: IC1.6 (~SEN), R4.2, R9.1
/RF_ANALOG_LOUT: C11.1, J5.9
/RF_ANALOG_ROUT: C10.1, J5.11
/RF_I2S_DCLK: IC1.17 (GPO3/[DCLK]), J5.3
/RF_I2S_DFS: IC1.16 (DFS), J5.5
/RF_I2S_DOUT: IC1.15 (DOUT), J5.7
GND: C1.2, C2.2, C3.2, C4.2, C6.2, C7.2, C8.2, IC1.3 (RFGND), IC1.12 (GND_1), IC1.21 (GND_2), J5.1, J5.4, J5.6, J5.8, J5.10, J5.12, J5.14, J5.16, J5.18, J5.20, R5.2, R6.2, U1.1 (GND), U2.9 (GND), U2.10 (IF-), U2.12 (GND), U2.17 (EP)
unnamed: C11.2, IC1.14 (LOUT/[DFS])
unnamed: C10.2, IC1.13 (ROUT/[DOUT])
unnamed: J5.15, R7.2
unnamed: J5.17, R8.2
unnamed: J5.19, R9.2
unnamed: J5.21, R10.2
unnamed: C9.2, L2.1
unnamed: C9.1, L1.1
unnamed: C5.2, R3.1, U2.15 (LO+)
unnamed: C6.1, R3.2, U2.14 (LO-)
unnamed: L1.2, U2.2 (RF+)
unnamed: L2.2, U2.3 (RF-)
